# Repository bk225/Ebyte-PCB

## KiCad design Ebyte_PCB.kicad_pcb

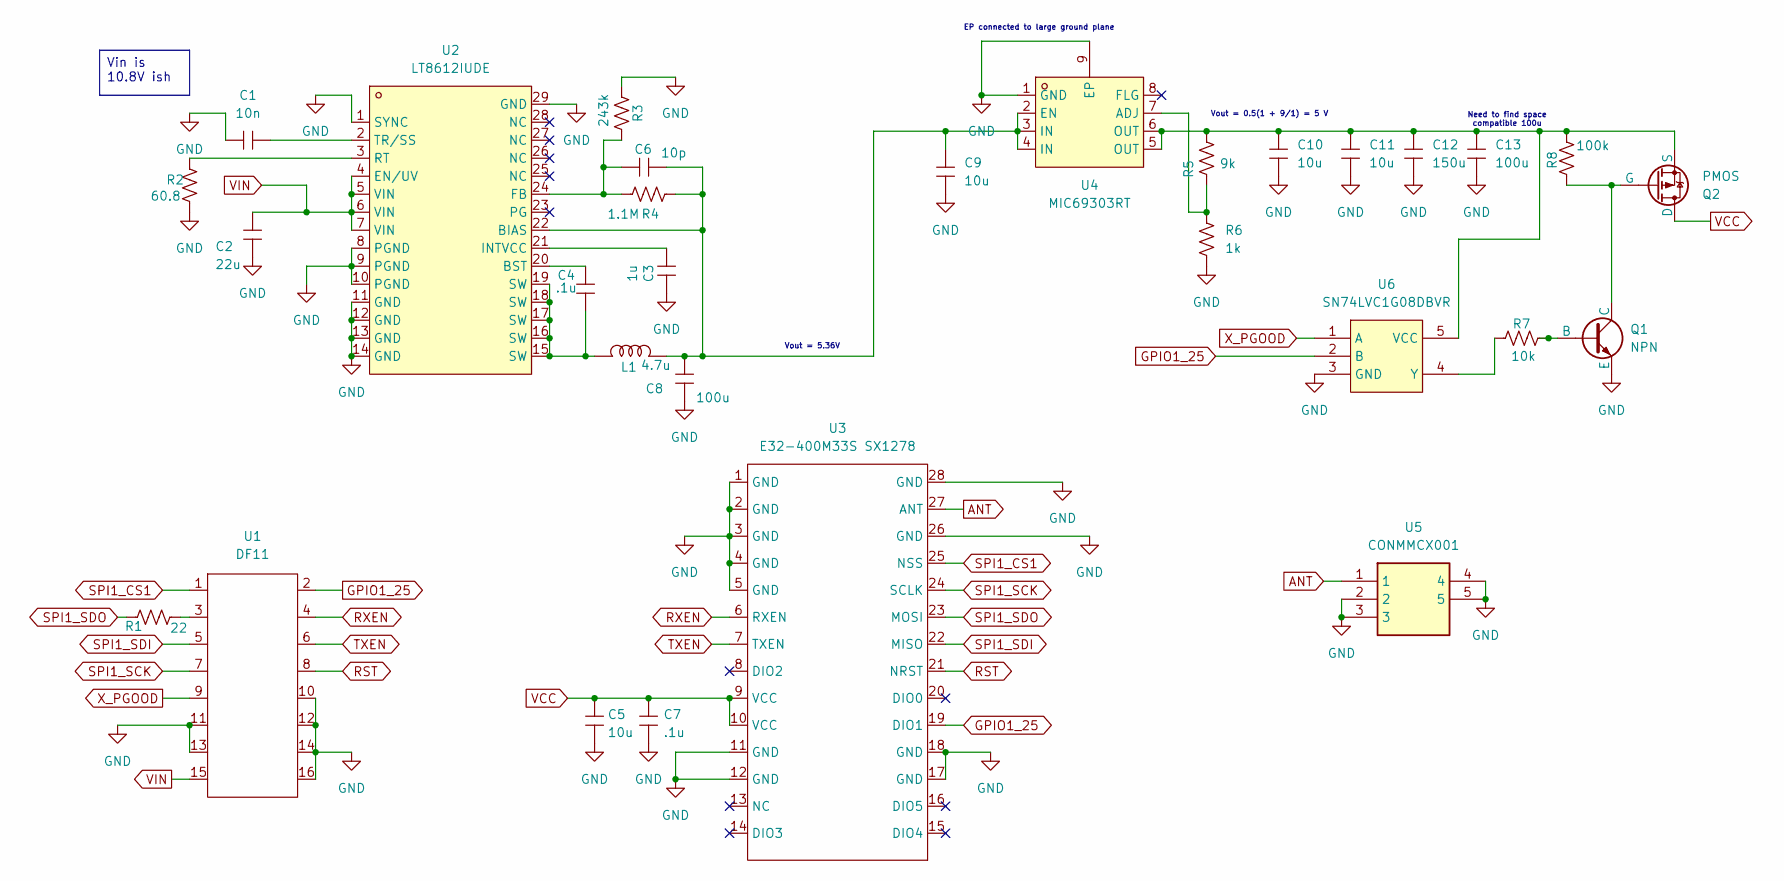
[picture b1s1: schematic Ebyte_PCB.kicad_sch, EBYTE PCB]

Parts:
C1: 10n; C0603
C2: 22u; C1210
C3: 1u; C0603
C4, C7: .1u; C0603
C5, C9, C10, C11: 10u; C1206
C6: 10p; C0603
C8, C13: 100u; CAP-SMD_L7.3-W4.3-R-RD
C12: 150u; CAP-SMD_BD6.3-L6.6-W6.6-FD
L1: 4.7u; IND-SMD_L5.4-W5.2_CMLE051E
Q1: NPN; SOT-23-5_L3.0-W1.7-P0.95-LS2.8-BR
Q2: PMOS; DFN-8_L5.1-W5.7-P1.27-LS6.1-BL
R1: 22; R0603
R2: 60.8; R0603
R3: 243k; R0603
R4: 1.1M; R0603
R5: 9k; R0603
R6: 1k; R0603
R7: 10k; R0603
R8: 100k; R0603
U1: DF11; Hirose_DF11-16DP-2DSA_2x08_P2.00mm_Vertical
U2: LT8612IUDE; QFN-28_L6.0-W3.0-P0.50-BL-EP
U3: E32-400M33S SX1278; E22-400M33S
U4: MIC69303RT; SOIC-8_L4.9-W3.9-P1.27-LS6.0-BL-EP
U5: CONMMCX001; Manufacturer_Part_Number CONMMCX001; Mouser Part Number N/A
U6: SN74LVC1G08DBVR; SOT-23-5_L3.0-W1.7-P0.95-LS2.8-BR

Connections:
ANT: U3.27 (ANT), U5.1
GND: C1.1, C2.1, C3.1, C5.1, C7.1, C8.1, C9.1, C10.1, C11.1, C12.1, C13.1, Q1.3 (E), R2.1, R3.1, R6.1, U1.10, U1.11, U1.12, U1.13, U1.14, U1.16, U2.1 (SYNC), U2.8 (PGND), U2.9 (PGND), U2.10 (PGND), U2.11 (GND), U2.12 (GND), U2.13 (GND), U2.14 (GND), U2.29 (GND), U3.1 (GND), U3.2 (GND), U3.3 (GND), U3.4 (GND), U3.5 (GND), U3.11 (GND), U3.12 (GND), U3.17 (GND), U3.18 (GND), U3.26 (GND), U3.28 (GND), U4.1 (GND), U4.9 (EP), U5.2, U5.3, U5.4, U5.5, U6.3 (GND)
GPIO1_25: U1.2, U3.19 (DIO1), U6.2 (B)
unnamed: C4.1, L1.1, U2.15 (SW), U2.16 (SW), U2.17 (SW), U2.18 (SW), U2.19 (SW)
unnamed: Q1.2 (B), R7.2
unnamed: Q1.1 (C), Q2.2 (G), R8.1
unnamed: C10.2, C11.2, C12.2, C13.2, Q2.3 (S), R5.2, R8.2, U4.5 (OUT), U4.6 (OUT), U6.5 (VCC)
unnamed: R1.2, U1.3
unnamed: C6.2, C8.2, C9.2, L1.2, R4.1, U2.22 (BIAS), U4.2 (EN), U4.3 (IN), U4.4 (IN)
unnamed: C4.2, U2.20 (BST)
unnamed: C6.1, R3.2, R4.2, U2.24 (FB)
unnamed: C3.2, U2.21 (INTVCC)
unnamed: R2.2, U2.3 (RT)
unnamed: C1.2, U2.2 (TR/SS)
unnamed: R5.1, R6.2, U4.7 (ADJ)
unnamed: R7.1, U6.4 (Y)
RST: U1.8, U3.21 (NRST)
RXEN: U1.4, U3.6 (RXEN)
SPI1_CS1: U1.1, U3.25 (NSS)
SPI1_SCK: U1.7, U3.24 (SCLK)
SPI1_SDI: U1.5, U3.22 (MISO)
SPI1_SDO: R1.1, U3.23 (MOSI)
TXEN: U1.6, U3.7 (TXEN)
VCC: C5.2, C7.2, Q2.1 (D), U3.9 (VCC), U3.10 (VCC)
VIN: C2.2, U1.15, U2.4 (EN/UV), U2.5 (VIN), U2.6 (VIN), U2.7 (VIN)
X_PGOOD: U1.9, U6.1 (A)

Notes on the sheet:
Need to find space compatible 100u
Vout = 0.5(1 + 9/1) = 5 V
Vout = 5.36V
EP connected to large ground plane
Vin is 10.8V ish

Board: 2 copper layers, 30 parts (0 on the bottom side), 26 nets, no tracks yet.

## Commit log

2026-04-23 Ebyte work
    my work on ebyte schematic and pcb so far
2026-04-23 Readding library files
